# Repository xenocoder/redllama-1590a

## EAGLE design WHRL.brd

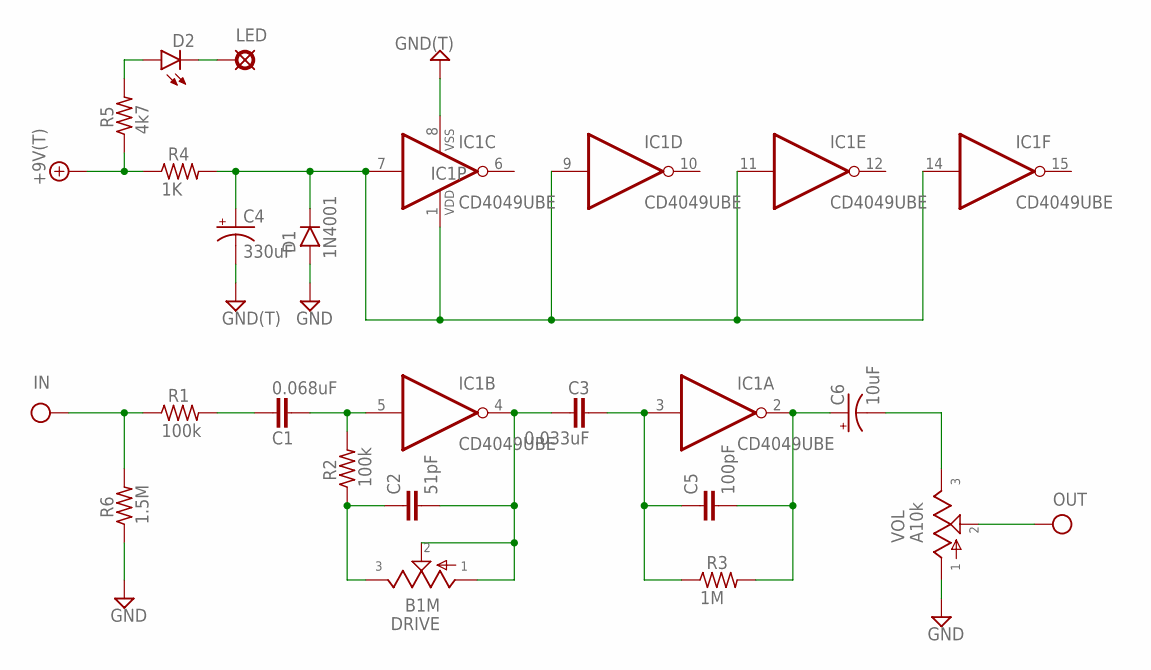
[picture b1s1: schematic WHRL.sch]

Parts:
+9V: +9V(T); SQUARE
C1: 0.068uF; 072X035
C2: 51pF; 050X030_025
C3: 0.033uF; 072X025
C4: 330uF; 080_035_1
C5: 100pF; 050X030_025
C6: 10uF; 050_020_1
D1: 1N4001; DO41-2
D2: LED3MM
DRIVE: B1M; POT_9MM_HOLES
G, G2: GND(T); SQUARE
IC1: CD4049UBE; DIL16
IN: IN(T); SQUARE
LED: PAD; SQUARE
OUT: OUT(T); SQUARE
R1, R2: 100k; R0204/2
R3: 1M; R0204/2
R4: 1K; R0204/2
R5: 4k7; R0204/2
R6: 1.5M; R0204/2
VOL: A10k; POT_9MM_HOLES

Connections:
+9V: +9V.1, R4.1, R5.1
GND: C4.-, D1.A, G.1, G2.1, IC1.8 (VSS), R6.1, VOL.P$1
IN: IN.1, R1.1, R6.2
unnamed: C4.+, D1.C, IC1.1 (VDD), IC1.7 (I), IC1.9 (I), IC1.11 (I), IC1.14 (I), R4.2
unnamed: D2.K (C), LED.1
unnamed: D2.A, R5.2
unnamed: C1.2, R1.2
unnamed: C1.1, IC1.5 (I), R2.2
unnamed: C2.2, C3.1, DRIVE.P$1, DRIVE.P$2, IC1.4 (O)
unnamed: C3.2, C5.1, IC1.3 (I), R3.1
unnamed: C5.2, C6.+, IC1.2 (O), R3.2
unnamed: C6.-, VOL.P$3
unnamed: OUT.1, VOL.P$2
unnamed: C2.1, DRIVE.P$3, R2.1

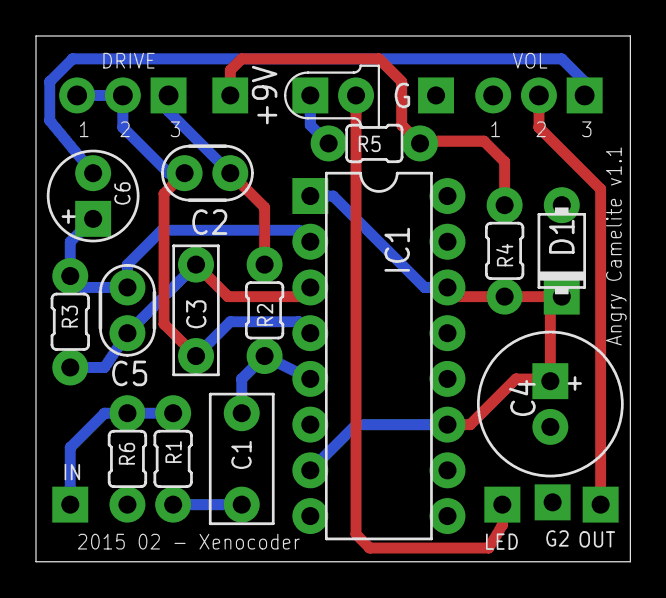
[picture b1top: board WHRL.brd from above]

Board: 2 copper layers, 33.0 x 29.2 mm, 23 parts (0 on the bottom side), 14 nets.

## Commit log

2015-12-26 Layout 1.0 sent to OSHPark.
2016-02-14 Rotated pots to right direction and rerouted traces. V1.1
